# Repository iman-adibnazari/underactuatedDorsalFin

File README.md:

## Overview
- Proposing an efficient fish robot design where, leveraging the physical properties of the dorsal fin material, only the front part of the fin is motor-driven to initiate wave propagation
- Design a linear quadratic regulator(LQR) and feedforward controller to manage the movement of the fish's fin

## Set up
Install necessary packages listed in requirements.txt:
`$ pip install -r requirements.txt`

## Robot Assembly

1. Laser-cut acrylic fin ray, fish body acrylic Frame, Fiberglass Panel
```
cad\Fish\FinRay.SLDPRT
cad\Fish\Body2.SLDPRT
cad\Fish\FIN.SLDPRT
```
2. Build silicone fin using 3D printed mold embedded with FR4 and fin ray 
```
cad\Fin Silicone Mold\Fin_mold_assemble.SLDASM
```
3. 3D printing PLA Head Closure 
```
cad\Fish\Body1_L.SLDPRT
cad\Fish\Body1_R.SLDPRT
```
4. Assemble 
- Mount dowel pin, Savox SW0250MGP motor with left Head Closure
- Attach fin with acrylic body frame
- Combine left head closure and acrylic body frame with fin 

## Control System Modeling
Goal: Aim to control the wave motion of the undulatory dorsal fin of robotic fish
Approach: Employing a frequency-response-based control system modeling method
1. Use top-view video data of the fish's fin, run `src\dataGenProc\multiObjectTracking.py` to calculate each position of the fin over time
2. Run `src\dataGenProc\GenerateBodedata.py` to create Bode plot using the processed video data
3. Run `src\dataGenProc\EstimateTF.m` in MATLAB to estimate Transfer Function from Bode plot, and generate discrete time state-space model
4. Design LQR gain, Kalman filter gain by running `src\dataGenProc\ControllerDesign.m` in MATLAB

## Testing Controller in Robotic Fish
1. Run `src\controlSystem\realTimeTracking.py` to track the tail point of the fin and send it to Arduino
2. Execute `src\controlSystem\discretecontroller\discretecontroller.ino` in Arduino IDE to output motor sine wave frequency

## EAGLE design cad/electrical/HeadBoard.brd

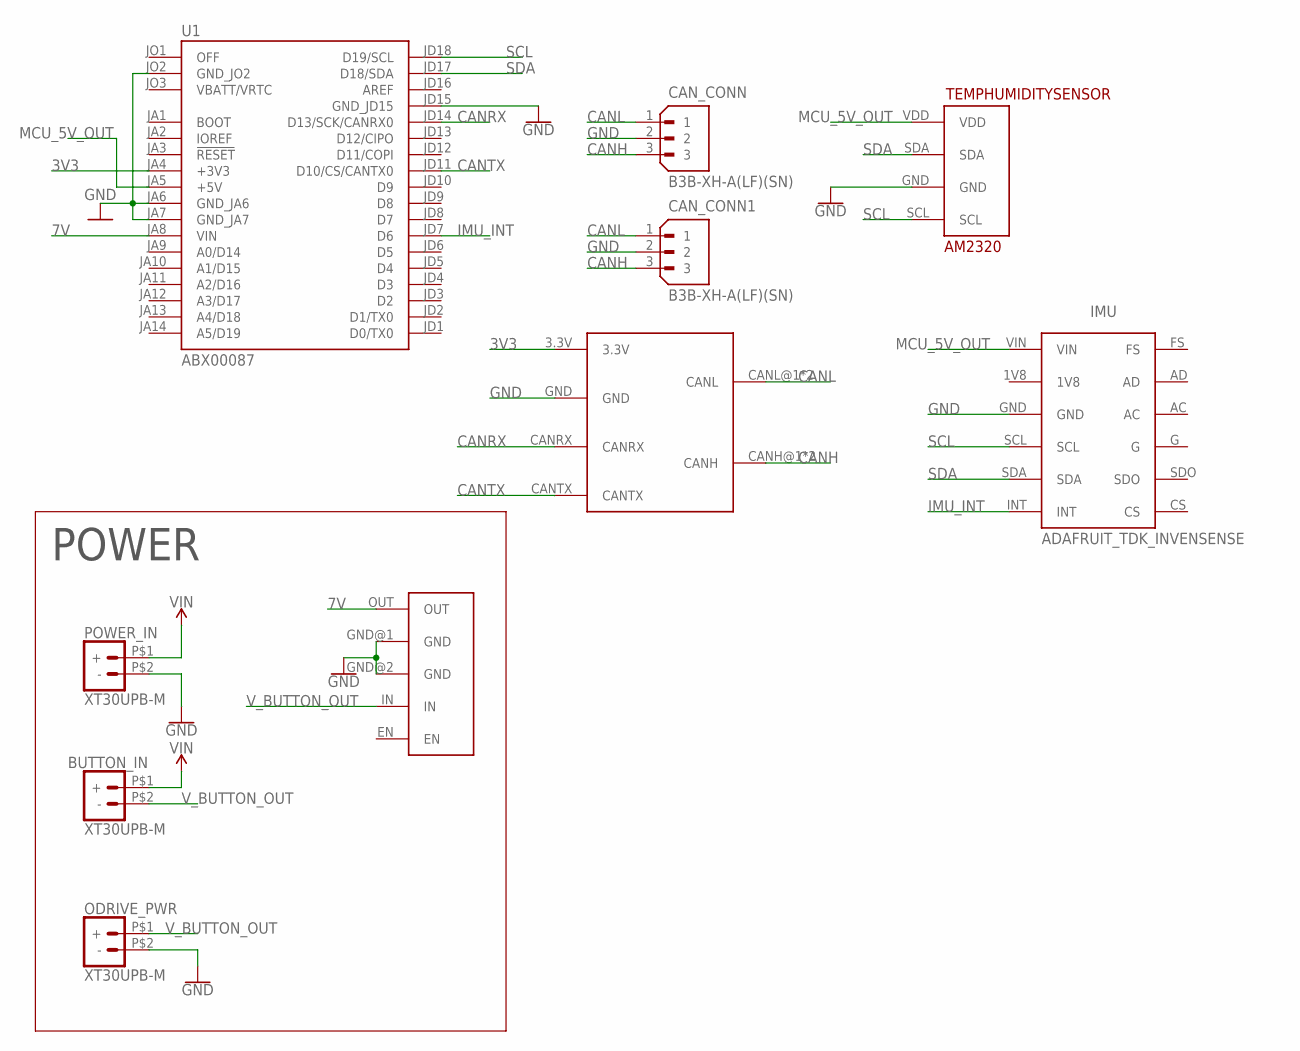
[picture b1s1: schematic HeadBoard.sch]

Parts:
BUTTON_IN: XT30UPB-M
CAN_CONN, CAN_CONN1: B3B-XH-A(LF)(SN); JST_B3B-XH-A(LF)(SN)
IMU: ADAFRUIT_TDK_INVENSENSE
ODRIVE_PWR: XT30UPB-M
POWER_IN: XT30UPB-M
TEMPHUMIDITYSENSOR: AM2320
U1: ABX00087; MODULE_ABX00087
U$1: D36V28F7; D36V28F5
U$2: WAVESHARE_SN65HVD230

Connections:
3V3: U1.JA4 (+3V3), U$2.3.3V
7V: U1.JA8 (VIN), U$1.OUT
CANH: CAN_CONN.3, CAN_CONN1.3, U$2.CANH@1 (CANH), U$2.CANH@2 (CANH)
CANL: CAN_CONN.1, CAN_CONN1.1, U$2.CANL@1 (CANL), U$2.CANL@2 (CANL)
CANRX: U1.JD14 (D13/SCK/CANRX0), U$2.CANRX
CANTX: U1.JD11 (D10/CS/CANTX0), U$2.CANTX
GND: CAN_CONN.2, CAN_CONN1.2, IMU.GND, ODRIVE_PWR.P$2 (-), POWER_IN.P$2 (-), TEMPHUMIDITYSENSOR.GND, U1.JA6 (GND_JA6), U1.JA7 (GND_JA7), U1.JD15 (GND_JD15), U1.JO2 (GND_JO2), U$1.GND@1 (GND), U$1.GND@2 (GND), U$2.GND
IMU_INT: IMU.INT, U1.JD7 (D6)
MCU_5V_OUT: IMU.VIN, TEMPHUMIDITYSENSOR.VDD, U1.JA5 (+5V)
SCL: IMU.SCL, TEMPHUMIDITYSENSOR.SCL, U1.JD18 (D19/SCL)
SDA: IMU.SDA, TEMPHUMIDITYSENSOR.SDA, U1.JD17 (D18/SDA)
VBATT/VRTC: U1.JO3 (VBATT/VRTC)
VIN: BUTTON_IN.P$1 (+), POWER_IN.P$1 (+)
V_BUTTON_OUT: BUTTON_IN.P$2 (-), ODRIVE_PWR.P$1 (+), U$1.IN

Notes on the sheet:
POWER

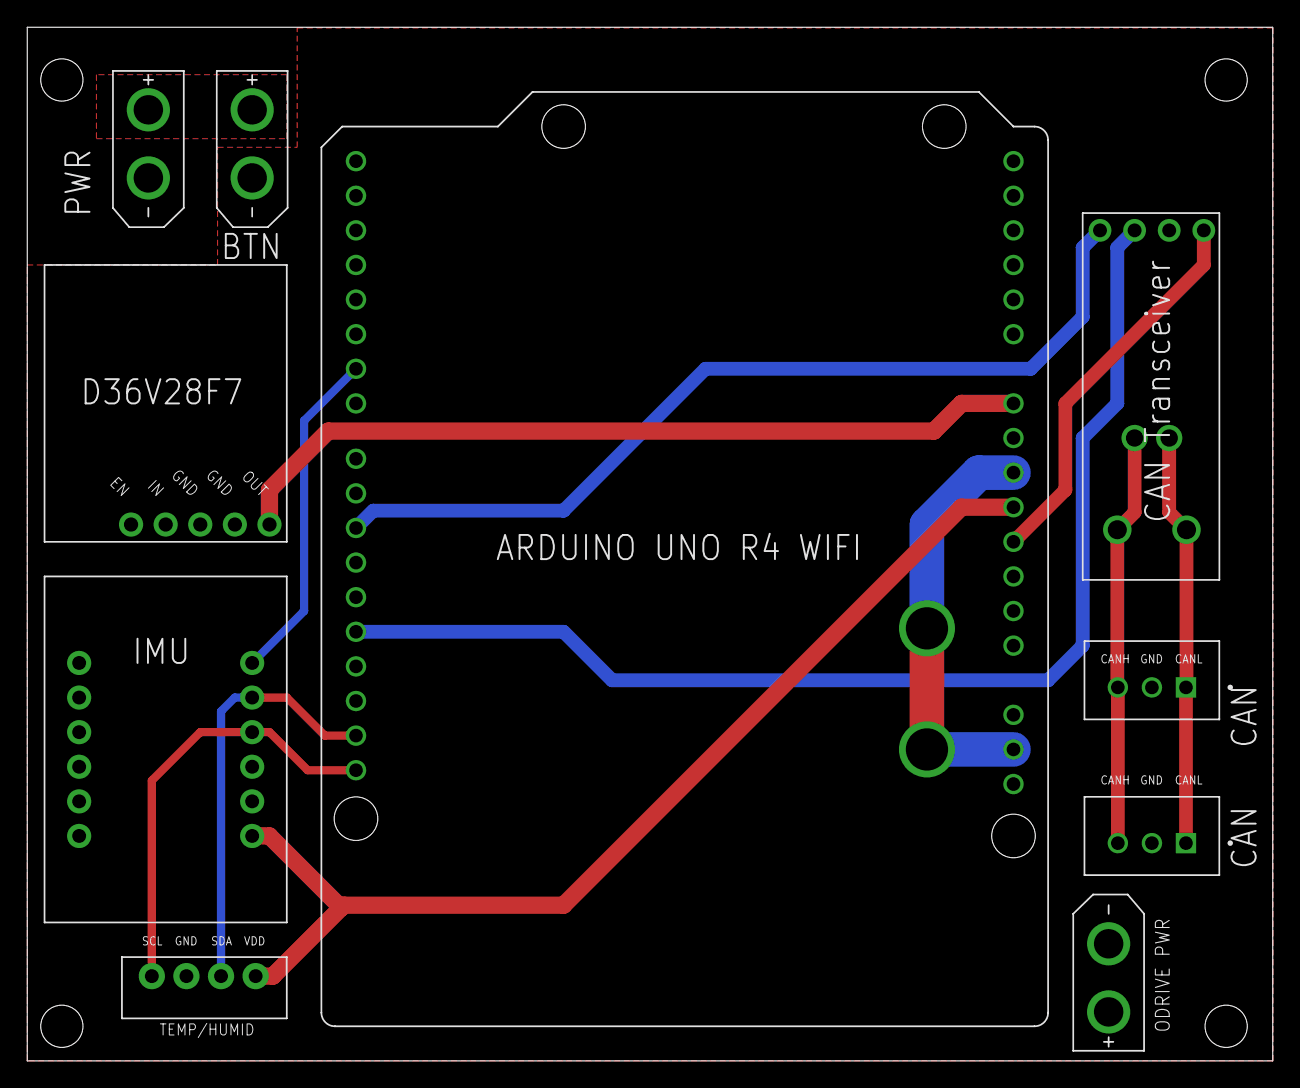
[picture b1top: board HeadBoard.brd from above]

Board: 2 copper layers, 91.4 x 75.9 mm, 10 parts (0 on the bottom side), 13 nets.

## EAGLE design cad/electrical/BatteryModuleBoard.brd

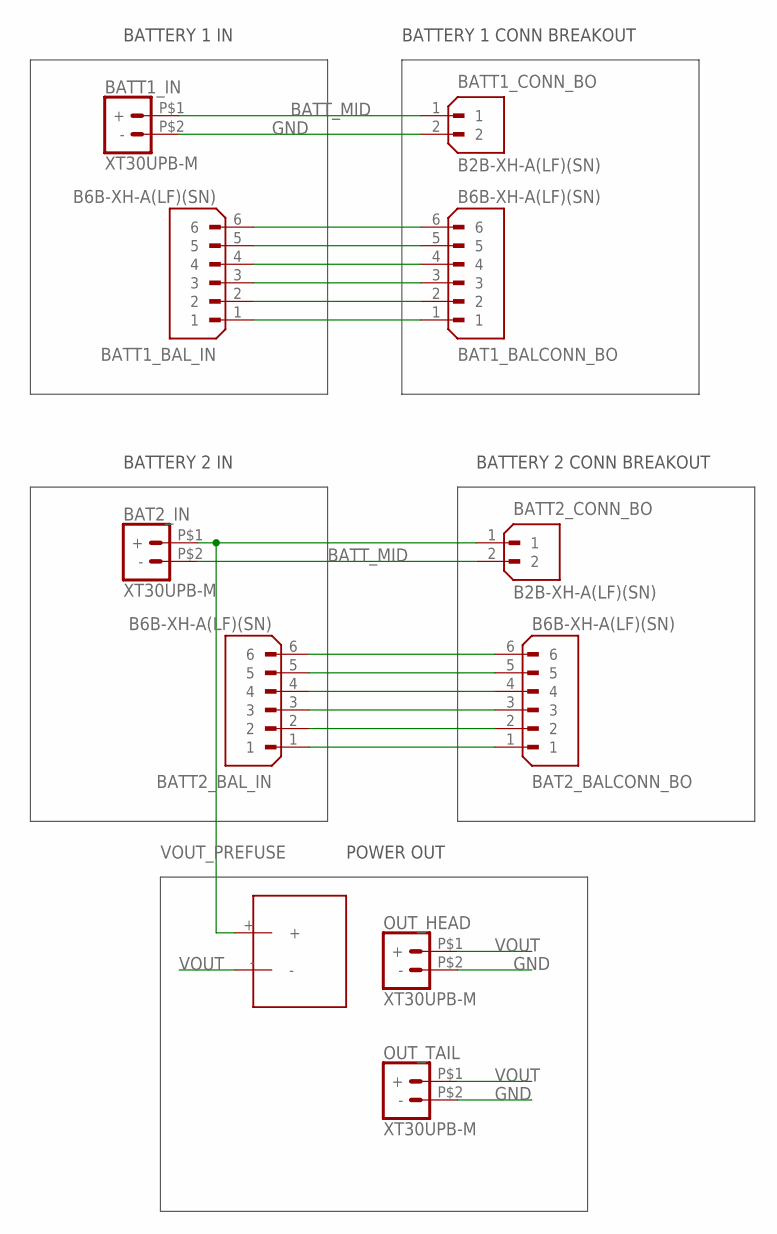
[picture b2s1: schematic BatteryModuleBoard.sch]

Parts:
BAT1_BALCONN_BO, BAT2_BALCONN_BO: B6B-XH-A(LF)(SN); JST_B6B-XH-A(LF)(SN)
BAT2_IN: XT30UPB-M
BATT1_BAL_IN, BATT2_BAL_IN: B6B-XH-A(LF)(SN); JST_B6B-XH-A(LF)(SN)
BATT1_CONN_BO, BATT2_CONN_BO: B2B-XH-A(LF)(SN); JST_B2B-XH-A(LF)(SN)
BATT1_IN: XT30UPB-M
FUSE: SETSAFE_C1_FUSE
OUT_HEAD: XT30UPB-M
OUT_TAIL: XT30UPB-M

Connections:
BATT_MID: BAT2_IN.P$2 (-), BATT1_CONN_BO.1, BATT1_IN.P$1 (+), BATT2_CONN_BO.2
GND: BATT1_CONN_BO.2, BATT1_IN.P$2 (-), OUT_HEAD.P$2 (-), OUT_TAIL.P$2 (-)
unnamed: BAT1_BALCONN_BO.6, BATT1_BAL_IN.6
unnamed: BAT1_BALCONN_BO.5, BATT1_BAL_IN.5
unnamed: BAT1_BALCONN_BO.4, BATT1_BAL_IN.4
unnamed: BAT1_BALCONN_BO.3, BATT1_BAL_IN.3
unnamed: BAT1_BALCONN_BO.2, BATT1_BAL_IN.2
unnamed: BAT1_BALCONN_BO.1, BATT1_BAL_IN.1
unnamed: BAT2_BALCONN_BO.6, BATT2_BAL_IN.6
unnamed: BAT2_BALCONN_BO.5, BATT2_BAL_IN.5
unnamed: BAT2_BALCONN_BO.4, BATT2_BAL_IN.4
unnamed: BAT2_BALCONN_BO.3, BATT2_BAL_IN.3
unnamed: BAT2_BALCONN_BO.2, BATT2_BAL_IN.2
unnamed: BAT2_BALCONN_BO.1, BATT2_BAL_IN.1
VOUT: FUSE.-, OUT_HEAD.P$1 (+), OUT_TAIL.P$1 (+)
VOUT_PREFUSE: BAT2_IN.P$1 (+), BATT2_CONN_BO.1, FUSE.+

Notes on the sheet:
BATTERY 1 IN
BATTERY 2 IN
BATTERY 1 CONN BREAKOUT
BATTERY 2 CONN BREAKOUT
POWER OUT

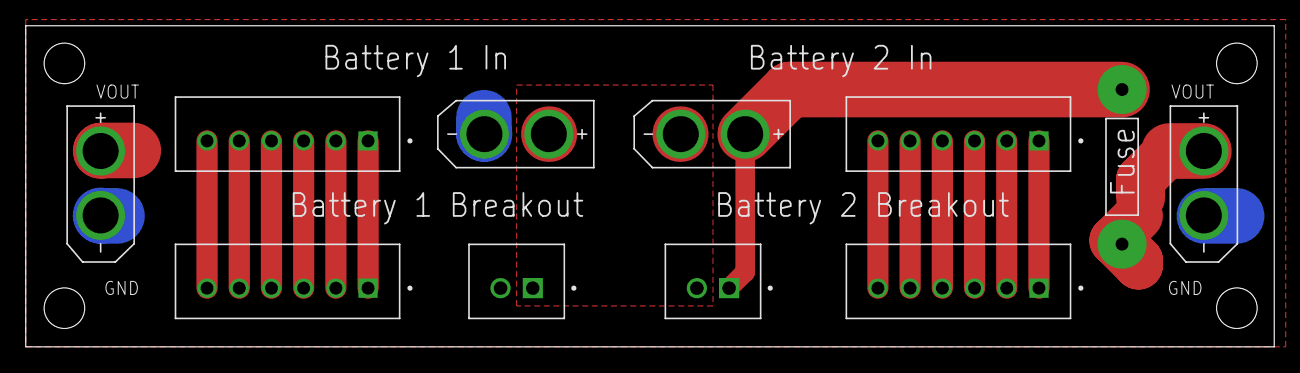
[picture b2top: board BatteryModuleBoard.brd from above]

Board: 2 copper layers, 96.9 x 24.9 mm, 11 parts (0 on the bottom side), 16 nets.

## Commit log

2023-11-13 add script for marker tracking with openCV
2023-12-09 Add matlab, python files for control system design
2023-12-09 Learning Git test
2023-12-09 test 2
2023-12-09 add scripts for real time visual tracking and communication with arduino over serial
2023-12-12 changed for plotting
2023-12-19 add folder for cad files
2024-01-04 Continuous to Discrete
2024-01-04 CAD files
2024-01-04 README test
2024-01-04 readme
2024-01-04 readme editted
2024-01-05 test
2024-01-05 Modified Readme, Arduino live code
2024-01-05 video
2024-07-13 Add script for controlling Odrive with Uno R4 Wifi
2024-09-11 update battery module board; add control boards for head modules
2024-09-11 Update pcb component sizes and power connections
2024-10-18 Generated fabrication files for RoboSoft deadline
2024-10-18 added examples for temp/humidity sensor and IMU on control board
2024-11-20 Update CAD and fab files to RAL fabrication version; add arduino examples for interfacing with components
2024-11-28 add docker services and files for mqtt control; add arduino file for mqtt control
2024-12-04 setup services and arduino code to control fish over MQTT
2024-12-04 add finite state machine to manage running state and command delays
2024-12-05 Update mqttControl.ino to compute joint angles
2024-12-06 update dualOdriveTest to run both odrives
2024-12-07 fix mqttControl to run ODrives remotely
2024-12-11 Add ArUco markers
2025-02-25 update fab files and create scripts for data processing
2025-04-23 update fab files; create notebook for processing data

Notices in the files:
parts and their libraries:
SparkFun-Aesthetics: Licensing: Creative Commons ShareAlike 4.0 International - https://creativecommons.org/licenses/by-sa/4.0
